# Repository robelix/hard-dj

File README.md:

# HardDJ - Arduino Mega based DJ MIDI Controller

using old Harddisks as jog wheels

Have a look to the wiki https://github.com/robelix/hard-dj/wiki for more documentation  

## Contents:

* arduino/libraries - Required arduino libs
* arduino/sketchbook - arduino code
* encoder - encoder wheels for lasercutting
* mixxx - MIDI-mapping for mixxx http://mixxx.org/
* eagle - sketches and pcbs
* ttymidi - serial to midi tool for linux

## License:
CC-BY-SA Roland "robelix" Obermayer <roland at robelix.com>
http://creativecommons.org/licenses/by-sa/3.0/at/

## Tools and libs with diffrent licenses

### Encoder wheel generator script
encoder/make_encoder.perl  
http://thedenneys.org/pub/robot/encoders/  
by Bryce Denney <bryce at tlw.com>  
License: GPL 2 or later  

### Arduino MIDI lib
arduino/libraries/MIDI/  
http://arduino.cc/playground/Main/MIDILibrary  
by Francois Best  
License: GPL  

### Arduino Encoder lib
arduino/libraries/Encoder/  
http://www.pjrc.com/teensy/td_libs_Encoder.html  
by PJRC.COM, LLC - Paul Stoffregen <paul@pjrc.com>  
License: MIT  

### ttymidi
ttymidi/  
http://www.varal.org/ttymidi/  
by Thiago Teixeira, Jari Suominen  
License GPL 3 or later

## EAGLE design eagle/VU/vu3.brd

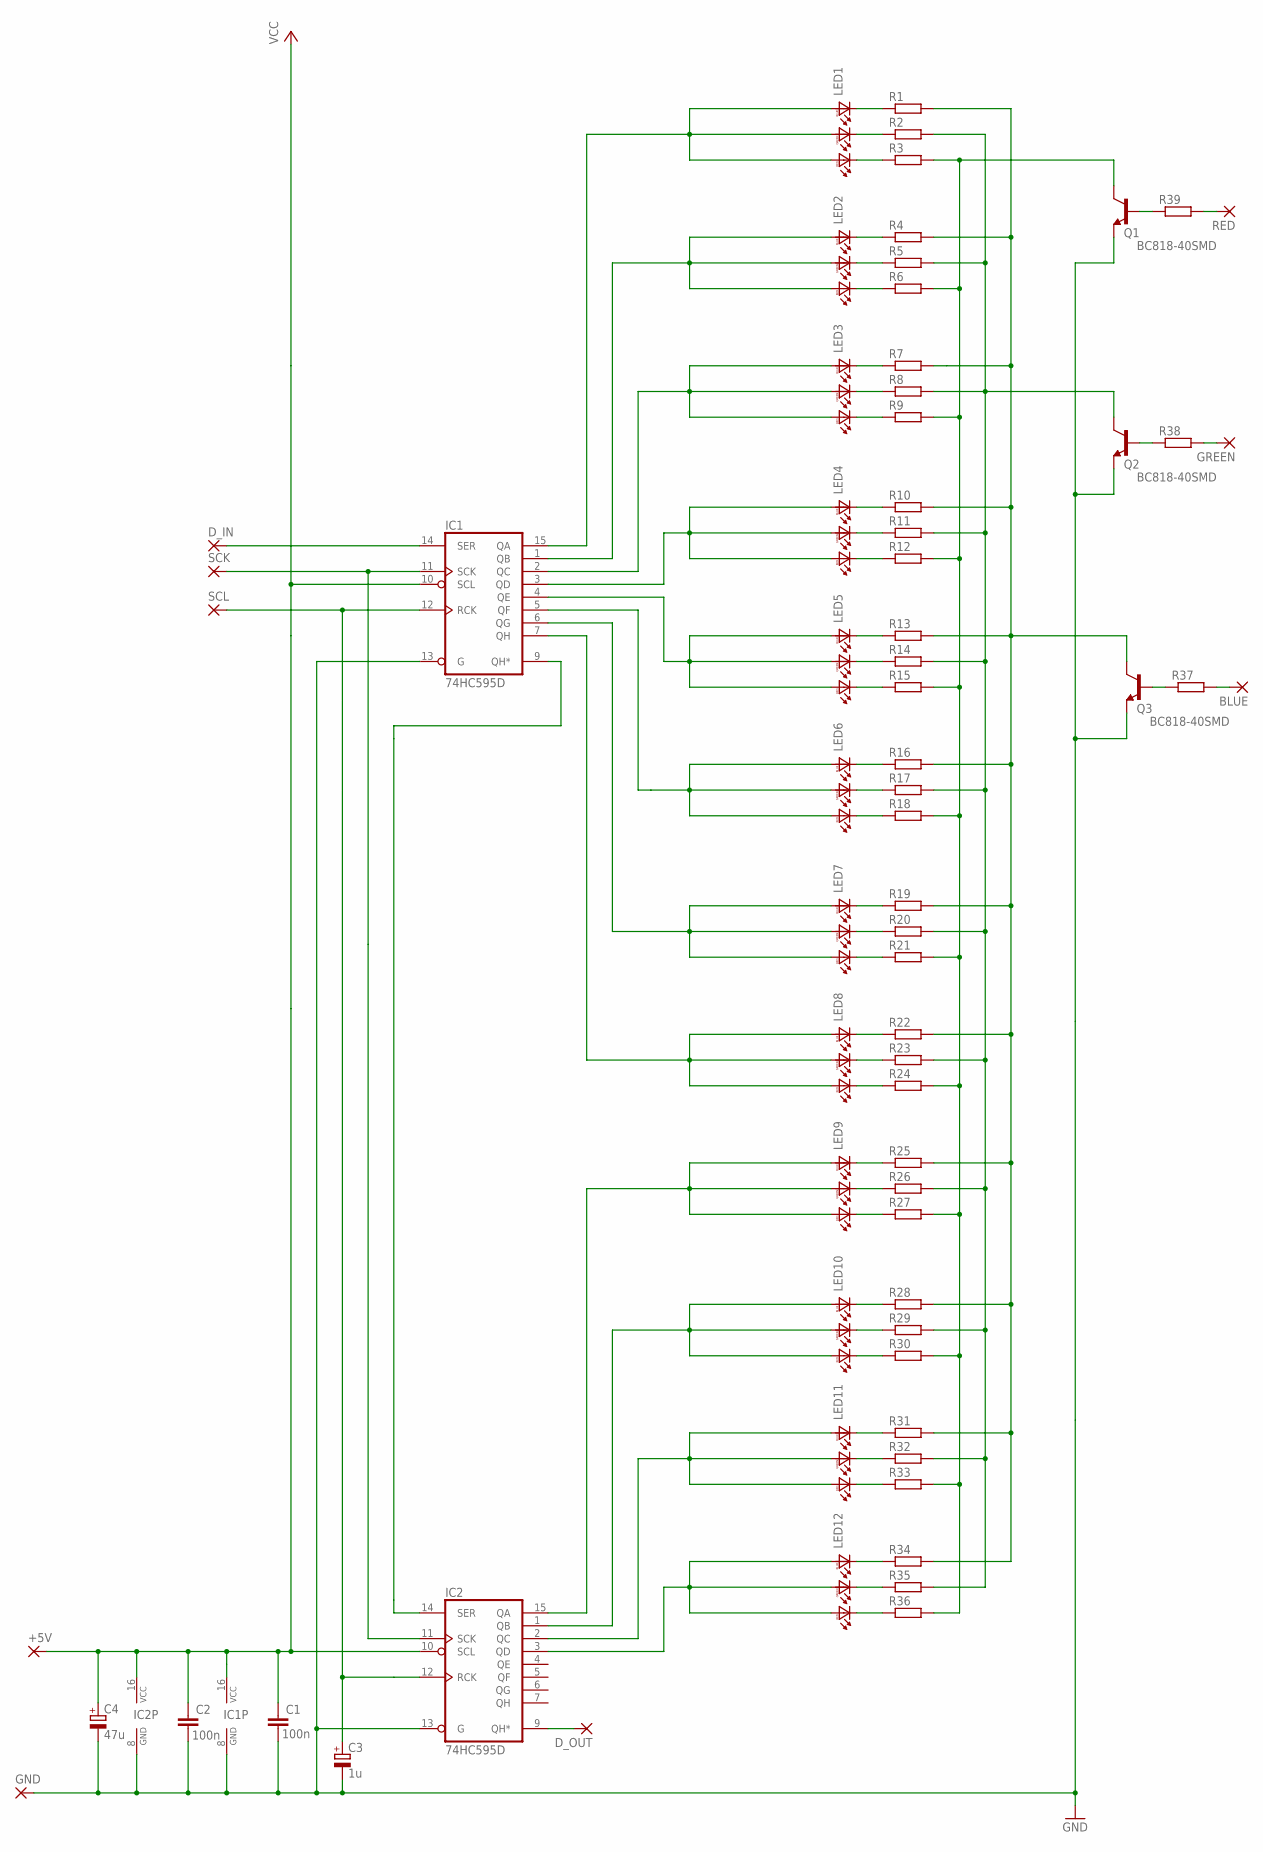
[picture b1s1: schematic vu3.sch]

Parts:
+5V: 2,54/0,8
BLUE: 2,54/0,8
C1, C2: 100n; C1206
C3: 1u; E5-5-L-12SMD
C4: 47u; E2,5-5-L-12SMD
D_IN: 2,54/0,8
D_OUT: 2,54/0,8
GND: 2,54/0,8
GREEN: 2,54/0,8
IC1, IC2: 74HC595D; SO16
LED1, LED2, LED3, LED4, LED5, LED6, LED7, LED8, LED9, LED10, LED11, LED12: LED_RGB_PLCC6; PLCC6
Q1, Q2, Q3: BC818-40SMD; SOT23-BEC
R1, R2, R3, R4, R5, R6, R7, R8, R9, R10, R11, R12, R13, R14, R15, R16, R17, R18, R19, R20, R21, R22, R23, R24, R25, R26, R27, R28, R29, R30, R31, R32, R33, R34, R35, R36, R37, R38, R39: R-EU_R1206; R1206
RED: 2,54/0,8
SCK: 2,54/0,8
SCL: 2,54/0,8

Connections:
unnamed: LED1.BC, R1.1
unnamed: R39.2, RED.1
unnamed: LED1.RC, R3.1
unnamed: LED2.GC, R5.1
unnamed: IC1.11 (SCK), IC2.11 (SCK), SCK.1
unnamed: LED3.BC, R7.1
unnamed: LED3.RC, R9.1
unnamed: +5V.1, C1.1, C2.1, C4.+, IC1.10 (SCL), IC1.16 (VCC), IC2.10 (SCL), IC2.16 (VCC)
unnamed: LED4.GC, R11.1
unnamed: IC2.15 (QA), LED9.BA, LED9.GA, LED9.RA
unnamed: LED5.BC, R13.1
unnamed: LED1.GC, R2.1
unnamed: LED5.RC, R15.1
unnamed: LED2.BC, R4.1
unnamed: LED6.GC, R17.1
unnamed: LED2.RC, R6.1
unnamed: LED7.BC, R19.1
unnamed: LED3.GC, R8.1
unnamed: LED7.RC, R21.1
unnamed: LED4.BC, R10.1
unnamed: LED8.GC, R23.1
unnamed: LED4.RC, R12.1
unnamed: LED9.BC, R25.1
unnamed: LED5.GC, R14.1
unnamed: LED9.RC, R27.1
unnamed: LED6.BC, R16.1
unnamed: LED10.GC, R29.1
unnamed: LED6.RC, R18.1
unnamed: LED11.BC, R31.1
unnamed: LED7.GC, R20.1
unnamed: LED11.RC, R33.1
unnamed: LED8.BC, R22.1
unnamed: LED12.GC, R35.1
unnamed: LED8.RC, R24.1
unnamed: LED9.GC, R26.1
unnamed: LED10.BC, R28.1
unnamed: LED10.RC, R30.1
unnamed: LED11.GC, R32.1
unnamed: LED12.BC, R34.1
unnamed: LED12.RC, R36.1
unnamed: GREEN.1, R38.2
unnamed: IC1.9 (QH*), IC2.14 (SER)
unnamed: Q3.B, R37.1
unnamed: BLUE.1, R37.2
unnamed: Q2.B, R38.1
unnamed: IC1.1 (QB), LED2.BA, LED2.GA, LED2.RA
unnamed: IC1.2 (QC), LED3.BA, LED3.GA, LED3.RA
unnamed: IC1.3 (QD), LED4.BA, LED4.GA, LED4.RA
unnamed: IC1.4 (QE), LED5.BA, LED5.GA, LED5.RA
unnamed: IC1.5 (QF), LED6.BA, LED6.GA, LED6.RA
unnamed: IC1.6 (QG), LED7.BA, LED7.GA, LED7.RA
unnamed: C1.2, C2.2, C3.-, C4.-, GND.1, IC1.8 (GND), IC1.13 (G), IC2.8 (GND), IC2.13 (G), Q1.E, Q2.E, Q3.E
unnamed: D_IN.1, IC1.14 (SER)
unnamed: IC1.7 (QH), LED8.BA, LED8.GA, LED8.RA
unnamed: Q1.B, R39.1
unnamed: Q3.C, R1.2, R4.2, R7.2, R10.2, R13.2, R16.2, R19.2, R22.2, R25.2, R28.2, R31.2, R34.2
unnamed: IC1.15 (QA), LED1.BA, LED1.GA, LED1.RA
unnamed: Q2.C, R2.2, R5.2, R8.2, R11.2, R14.2, R17.2, R20.2, R23.2, R26.2, R29.2, R32.2, R35.2
unnamed: C3.+, IC1.12 (RCK), IC2.12 (RCK), SCL.1
unnamed: D_OUT.1, IC2.9 (QH*)
unnamed: Q1.C, R3.2, R6.2, R9.2, R12.2, R15.2, R18.2, R21.2, R24.2, R27.2, R30.2, R33.2, R36.2
unnamed: IC2.1 (QB), LED10.BA, LED10.GA, LED10.RA
unnamed: IC2.2 (QC), LED11.BA, LED11.GA, LED11.RA
unnamed: IC2.3 (QD), LED12.BA, LED12.GA, LED12.RA

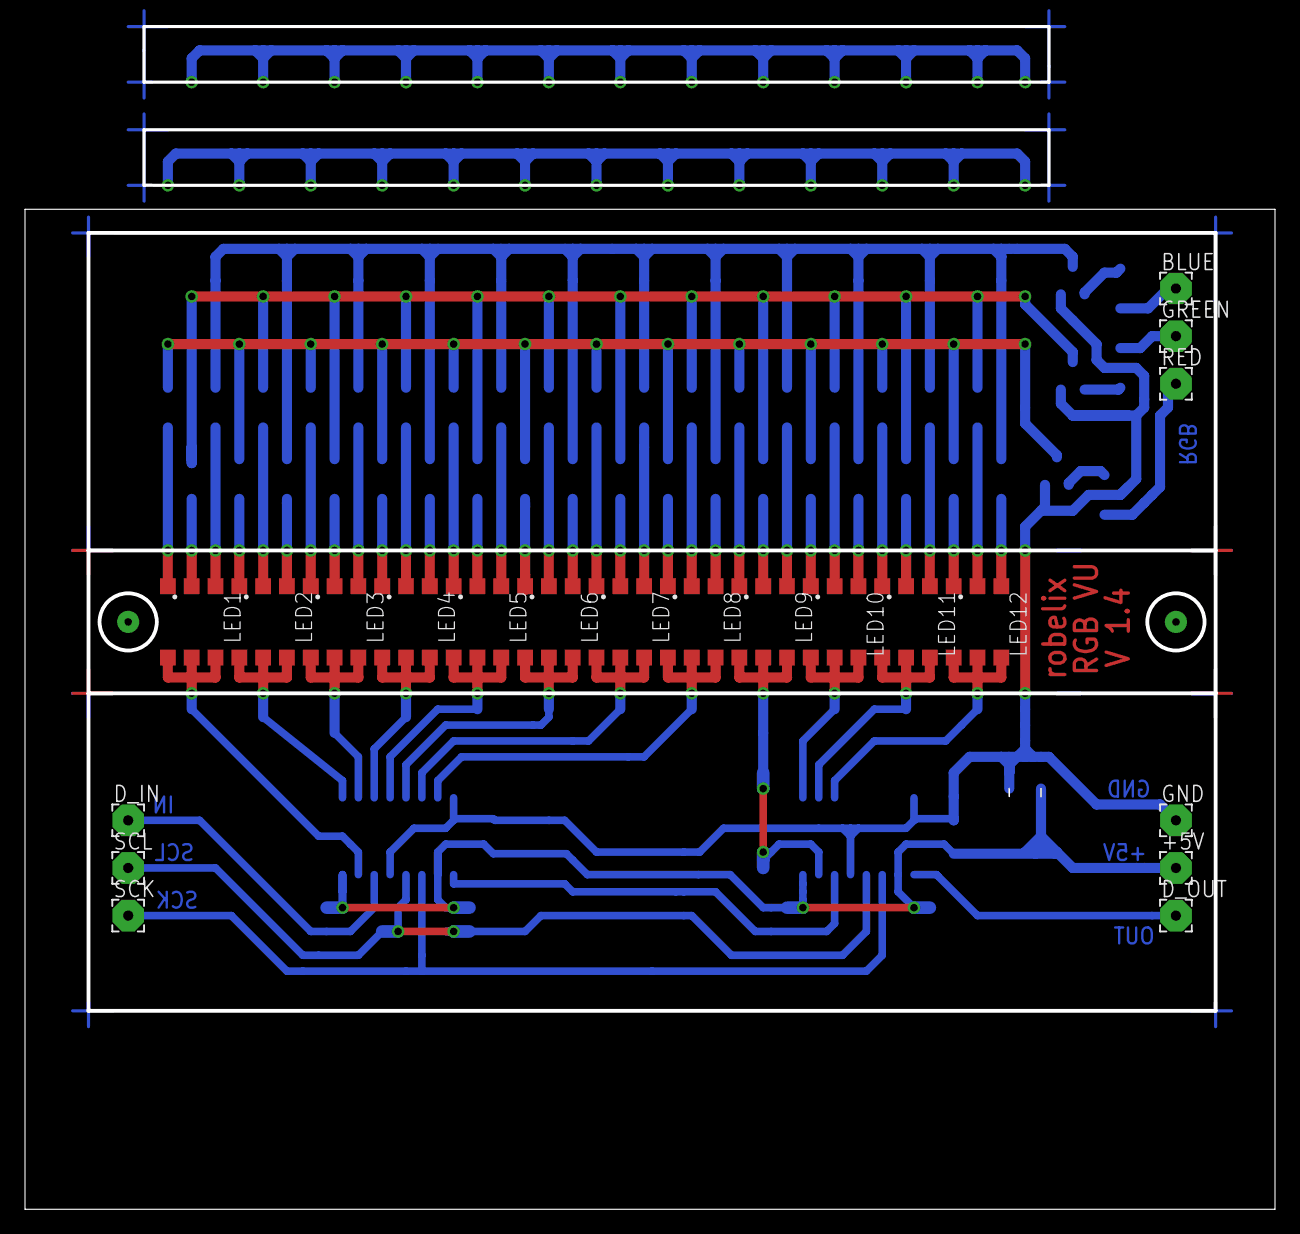
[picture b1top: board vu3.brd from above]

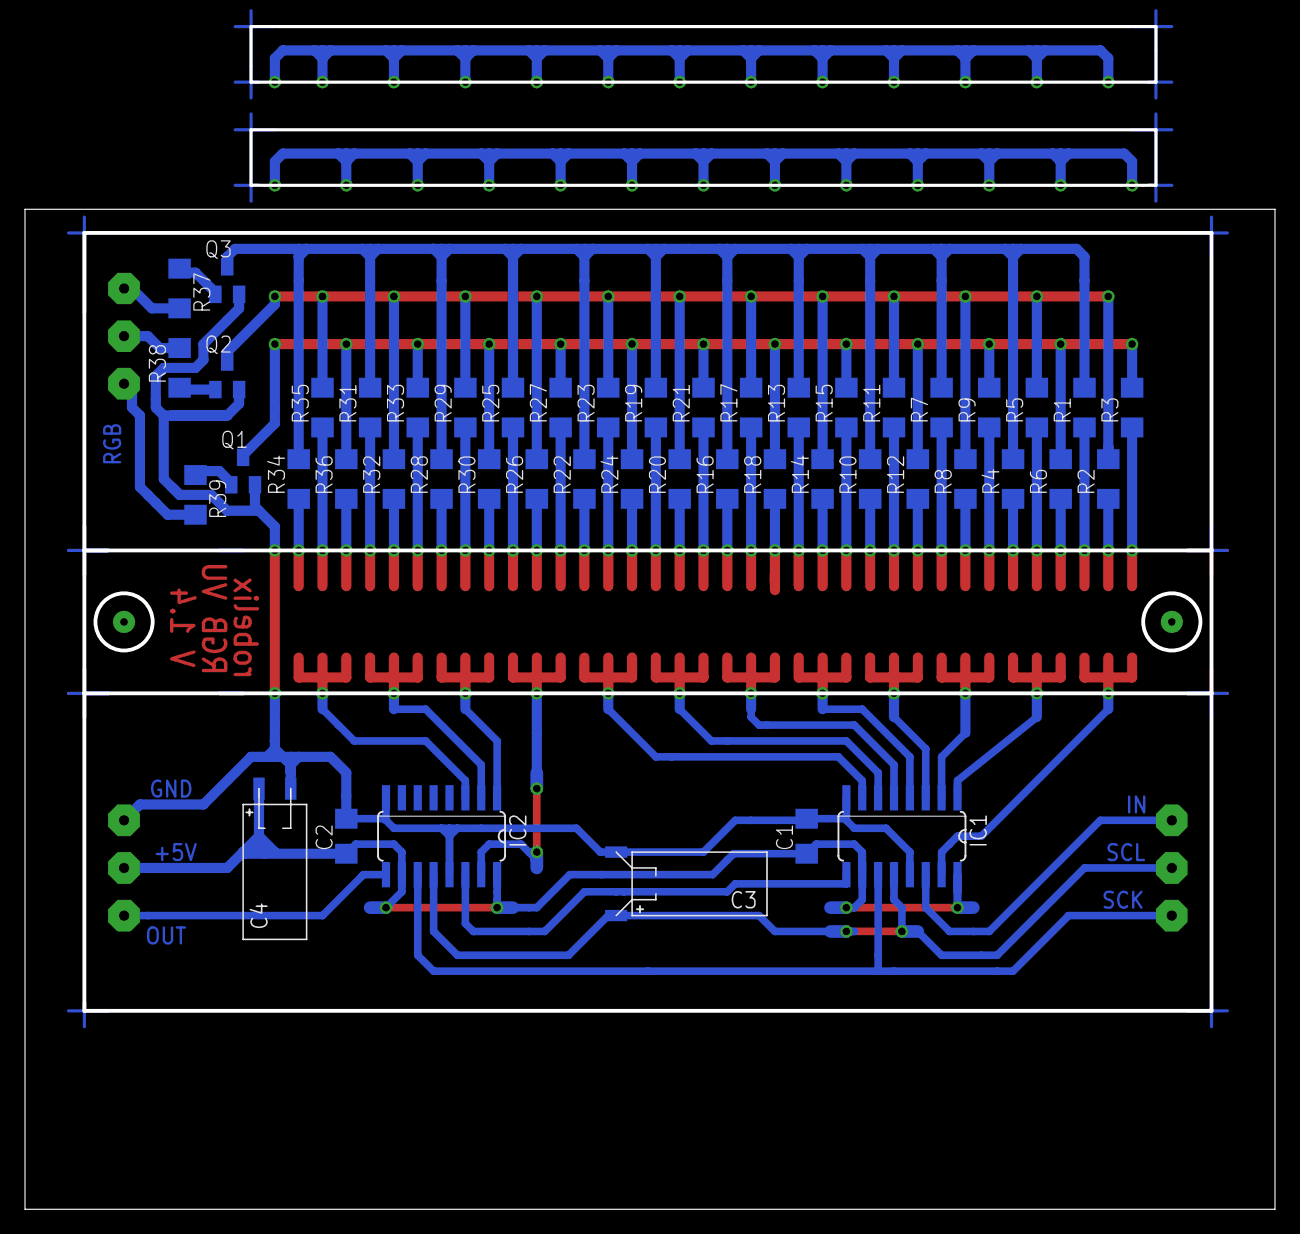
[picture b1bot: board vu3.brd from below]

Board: 2 copper layers, 100.0 x 80.0 mm, 69 parts (48 on the bottom side), 64 nets.

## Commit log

2012-05-13 Enocder-script & Encoder Files added
2012-05-17 first controller software - faders, potis, encoders, buttons
2012-05-17 eagle sketches of encoder & potis
2012-05-17 first mixxx mappings
2012-05-17 .gitignore
2012-05-17 renamed to arduino-compativle
2012-05-17 Encoder library from http://www.pjrc.com/teensy/td_libs_Encoder.html added
2012-05-17 using optimized encoder
2012-05-18 arduino midi lib 3.2 added
2012-05-18 first success with midi-sending - play leds
2012-06-02 first working vu
2012-06-15 Readme added
2012-07-08 keymatrix added, single-keys removed
2012-07-09 shift registers for leds
2012-07-09 mixxx-mappings for small keypads and some leds
2012-07-15 case leds added
2012-08-06 corrected potis mapping
2012-08-06 filename and include changed to work with arduino 1.0.x
2012-08-06 Corrected Pin numbers in sketches
2012-08-06 keymatrix sketch
2012-08-22 ttymidi added
2012-08-22 device strings changed in ttymidi - if they are not the same for in and out mixxx thinks these are diffrent devices
2012-08-30 additional buttons and leds
2012-08-31 mixxx midi bindings for the added buttons and some cleanup of duplicate functions
2013-08-25 RGB-VUs added
2018-10-22 Update Makefile
    Added the parameter -lpthread solve “error adding symbols: DSO missing from command line” while compiling on newest systems
